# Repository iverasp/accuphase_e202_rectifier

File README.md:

# Full wave rectifier for the Accuphase E-202

Using MUR820 diodes and filter capacitors in parallel.

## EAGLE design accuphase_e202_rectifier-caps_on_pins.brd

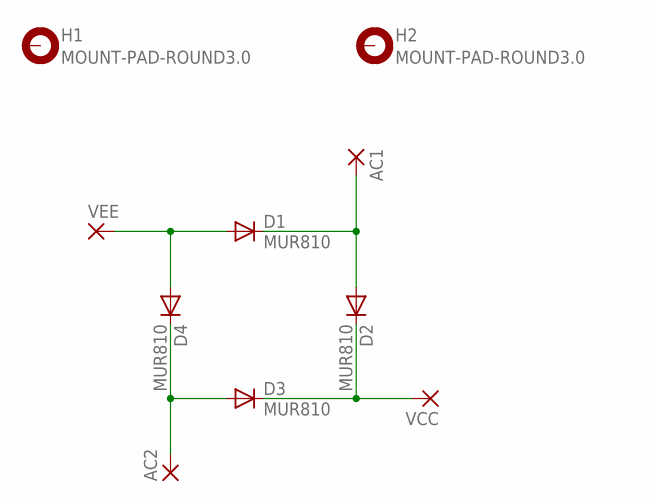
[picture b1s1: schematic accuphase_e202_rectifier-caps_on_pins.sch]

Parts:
AC1, AC2: 3,81/1,4
D1, D2, D3, D4: MUR810; TO220ACS
H1, H2: MOUNT-PAD-ROUND3.0; 3,0-PAD
VCC: 3,81/1,4
VEE: 3,81/1,4

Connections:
unnamed: AC1.1, D1.C, D2.A
unnamed: D2.C, D3.C, VCC.1
unnamed: AC2.1, D3.A, D4.C
unnamed: D1.A, D4.A, VEE.1

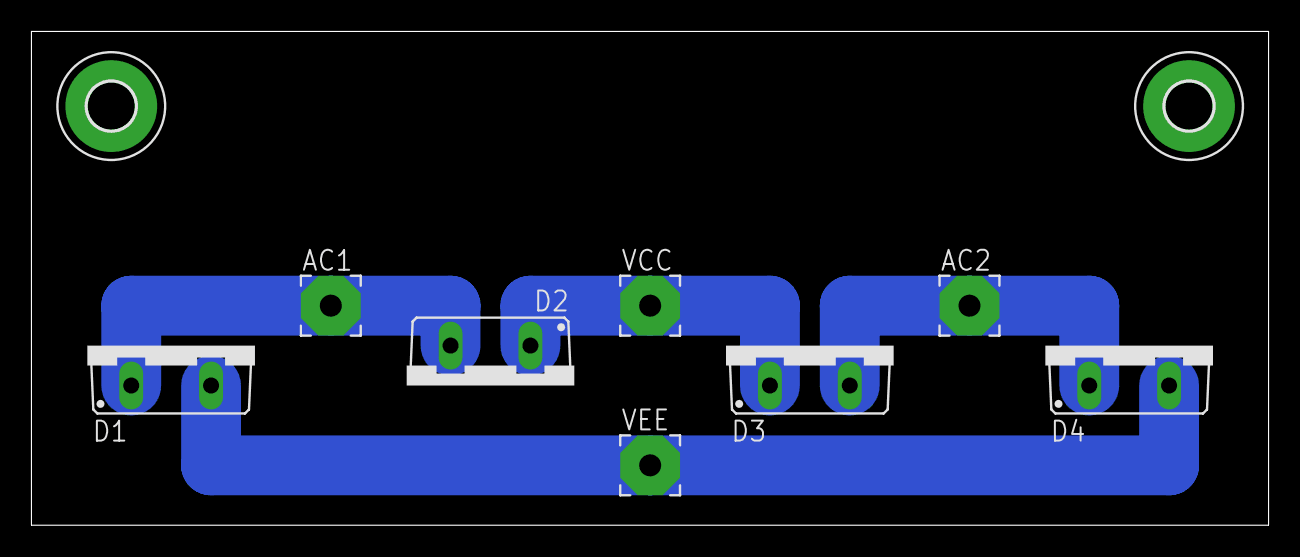
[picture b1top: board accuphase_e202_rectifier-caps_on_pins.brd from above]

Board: 2 copper layers, 78.7 x 31.4 mm, 10 parts (0 on the bottom side), 4 nets.

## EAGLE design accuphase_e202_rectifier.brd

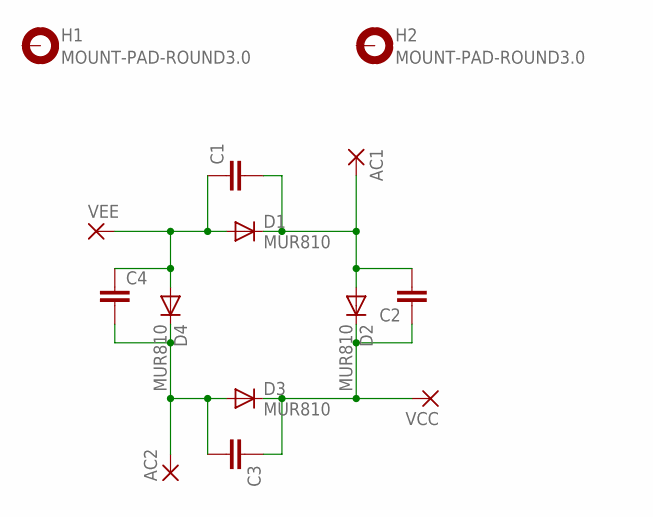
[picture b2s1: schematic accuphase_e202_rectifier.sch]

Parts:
AC1, AC2: 3,81/1,4
C1, C2, C3, C4: C-EU075-032X103; C075-032X103
D1, D2, D3, D4: MUR810; TO220ACS
H1, H2: MOUNT-PAD-ROUND3.0; 3,0-PAD
VCC: 3,81/1,4
VEE: 3,81/1,4

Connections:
unnamed: AC1.1, C1.2, C2.2, D1.C, D2.A
unnamed: C2.1, C3.1, D2.C, D3.C, VCC.1
unnamed: AC2.1, C3.2, C4.2, D3.A, D4.C
unnamed: C1.1, C4.1, D1.A, D4.A, VEE.1

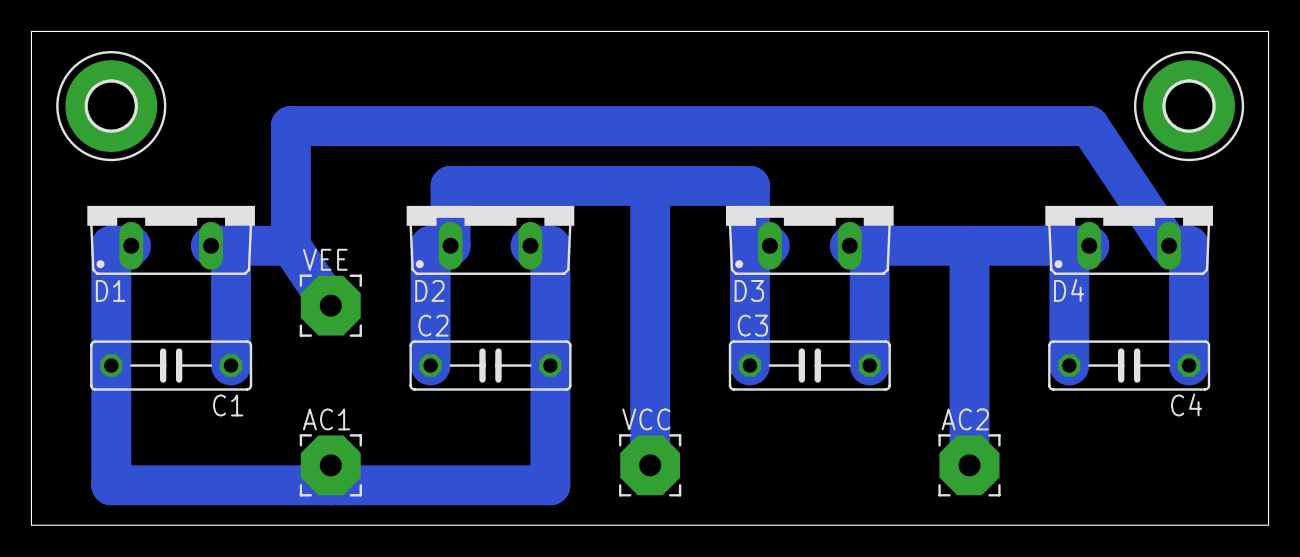
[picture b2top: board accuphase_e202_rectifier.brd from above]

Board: 2 copper layers, 78.7 x 31.4 mm, 14 parts (0 on the bottom side), 4 nets.

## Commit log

2015-10-18 added gitignore
2015-10-18 added schematic
2015-10-18 added pcb
2015-10-19 minor improvement
2015-10-19 caps soldered directly to pins on diodes. better spacing
2015-10-19 wider tracks
